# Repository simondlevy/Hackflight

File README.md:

# Intro

Hackflight is a minimalist software toolkit for building multirotor flight
controllers and simulators.  It is geared toward people like me who want to
tinker with flight-control firmware, and use it to teach students about ideas
like
[state estimation](https://simondlevy.github.io/ekf-tutorial)
and
[PID control](https://en.wikipedia.org/wiki/Proportional%E2%80%93integral%E2%80%93derivative_controller).
<b>If you are in the 99% percent of
users who just want to get your vehicle flying without getting into firmware
hacking, I recommend [Betaflight](http://betaflight.com/)</b> (great for
getting started when you're on a budget)
<b>the [Ardupilot](http://copter.ardupilot.org) system</b> (for
sophisticated mission planning with waypoint navigation and the like), or
the <b>[Crazyflie](https://www.bitcraze.io/products/old-products/crazyflie-2-1/)</b>
platform, for a safe, inexpensive introduction to quadcopters as a research
platform.   In addition to big user communities and loads of great features,
these platforms have safety mechanisms that Hackflight lacks, which will help
avoid injury to you and damage to your vehicle.

# Design principles

Hackflight attempts to maintain a simple relationship between
the code and the elements of the flight-control dataflow diagram shown below.
Boxes represent data, ovals represent functions, and feedback arrows
represent the need for functions that have state; for
example, the maintenance of an error integral in a PID controller:

By using header-only C++ classes whenever possible, avoiding C-style macros,
[null pointers](https://www.infoq.com/presentations/Null-References-The-Billion-Dollar-Mistake-Tony-Hoare/),
inheritance, and mutation in favor of
[functional style](https://queue.acm.org/detail.cfm?id=2038036i),
and relying on existing Arduino libraries for sensors and actuators,
Hackflight supports a
[composable](https://www.progress.com/blogs/what-composability-why-should-you-care)
approach to taming the complexity of flight control. The Hackflight [codebase](src/) is
under 3,000 lines of code.

# Hardware

* MCU: [Teensy4.0](https://www.pjrc.com/store/teensy40.html)

* IMU: [BMI088 I^2C breakout board](https://www.tindie.com/products/bobbiebots/bmi088-i2c-breakout)

* Receiver: [OMGS3 ESP32](https://unexpectedmaker.com/shop.html#!/OMGS3/p/687192227)

* Transmitter: Radiomaster T8L modified with [custom circuit board](kicad/tx) using
[TinyS3 ESP32](https://www.adafruit.com/product/5398)

* Telemetry dongle: [TinyPICO ESP32](https://www.adafruit.com/product/5028)

# Simulator

For flight simulation, Hackflight uses [Webots](https://cyberbotics.com/),
a free, open-source robotics simulator. Click [here](webots/apex2) to get started.

# Citing Hackflight

Please cite Hackflight as:

```
@ARTICLE{10.3389/fnbot.2020.00016,
AUTHOR={Levy, Simon D.},   
TITLE={Robustness Through Simplicity: A Minimalist Gateway to Neurorobotic Flight},      
JOURNAL={Frontiers in Neurorobotics},      
VOLUME={14},           
YEAR={2020},      
URL={https://www.frontiersin.org/articles/10.3389/fnbot.2020.00016},       
DOI={10.3389/fnbot.2020.00016},      
ISSN={1662-5218}
}
```

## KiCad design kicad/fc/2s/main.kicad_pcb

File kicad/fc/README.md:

# BOM

* 4-in-1 ESC with motor/power connector and rubber grommets

* Teensy 4.0

* BMI088 breakout

* [Pololu 5V Step-Up/Step-Down Voltage Regulator S7V7F5](https://www.pololu.com/product/2119)

* [1.25mm Pitch JST Molex Picoblade connectors and Pre-Crimped Cables](https://www.amazon.com/dp/B07S18D3RN)

* [LED](https://lighthouseleds.com/1-8mm-2mm-led-red-ultra-bright.html)

* [8-pin 1.25mm Pitch JST Molex Picoblade connector, male pins, right angle](https://www.digikey.com/en/products/detail/molex/0530480810/242870)

* [M2 nylon screws, nuts, and standoffs](https://www.amazon.com/dp/B07D78PFQL)

* Resistors: 100 Ohm, 1000 Ohm, 3300 Ohm

* 1x14 0.1" pitch male header pins

# Build instuctions

Note: I recommend using Scotch tape to mask the pins you're not currently
soldering, and doing a continuity check for bridges/shorts after each step.

Main Board

1. Solder BMI088 breakout to front of board.

2. Solder voltage regulator on back.

3. Solder 1x14 headers on front.

4. Solder the three resistors on back.

5. Solder the LED on front

6. Solder the 4-in-1 ESC cables on the bottom.

7. Build the hover-deck cable using an 8-pin Picoblade connector and pre-crimped cables.

8. Mount the flight controller to the airframe with four M2 screws and nuts, and rubber grommets.

9. After covering the Teensy 4.00 bottom middle with electrical tape to
insulate it from any conact with the components on the flight controller,
solder the Teensy 4.0 onto the header pins on the flight controller. 

Hover Deck: Solder right-angle male PicoBlade connector to board

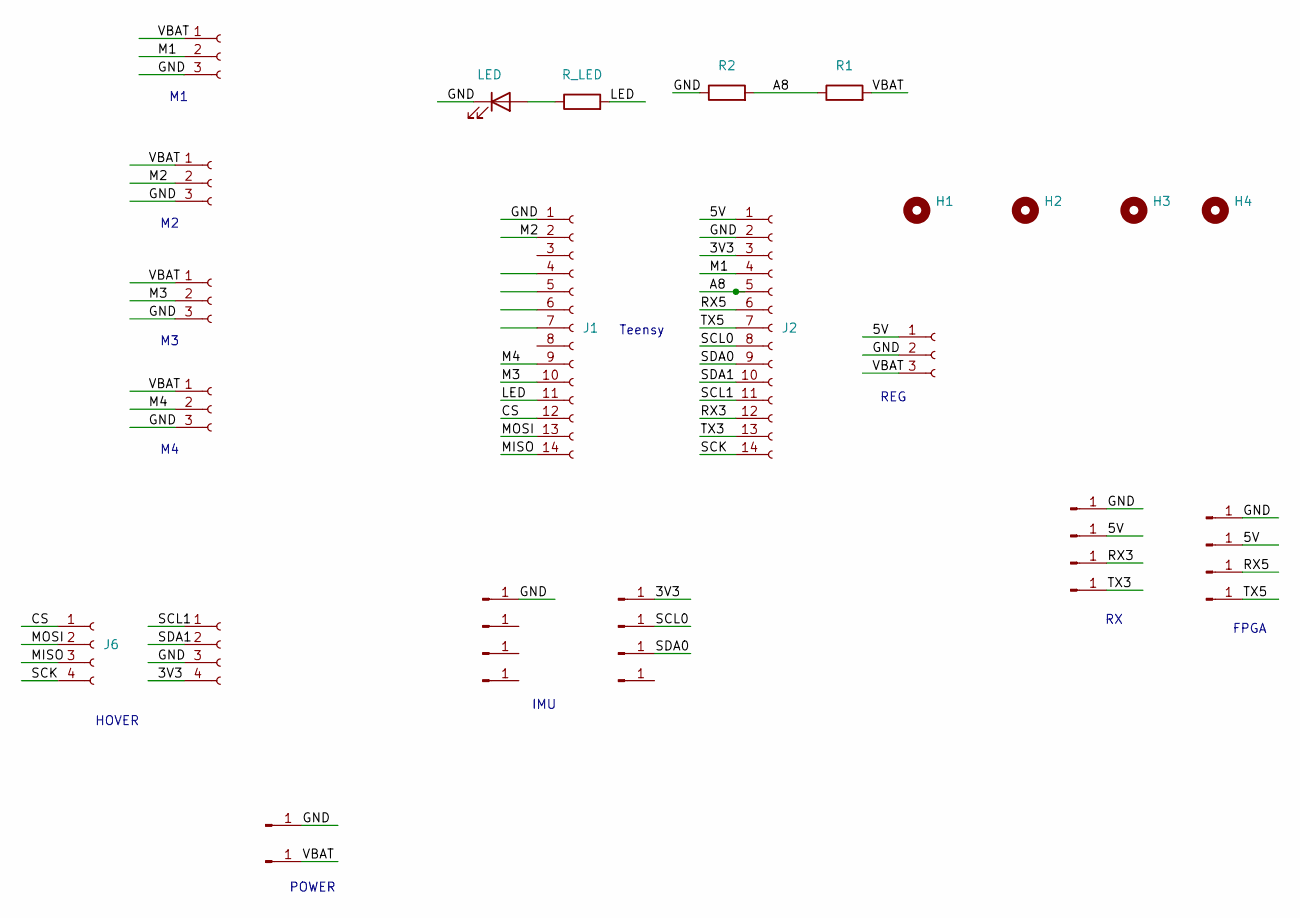
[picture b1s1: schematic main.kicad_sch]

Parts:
D1: LED; LED_D3.0mm_FlatTop
H1, H2, H3, H4: MountingHole; MountingHole_2.5mm
J1: Conn_01x14; PinSocket_1x14_P2.54mm_Vertical
J2: Conn_01x14_Socket; PinSocket_1x14_P2.54mm_Vertical
J3, J5, J7, J8, J9, J10, J11, J12, J13, J14, J17, J18, J19, J20, J21, J22: Conn_01x01_Pin; SolderWirePad_1x01_SMD_1x2mm
J4, J15, J16, J23, J24: Conn_01x03_Socket; PinHeader_1x03_P2.54mm_Vertical
J6, J27: Conn_01x04_Socket; PinHeader_1x04_P2.54mm_Vertical
J25, J26: Conn_01x01_Pin; SolderWirePad_1x01_SMD_2x4mm
R1: R_LED; R_Axial_DIN0204_L3.6mm_D1.6mm_P7.62mm_Horizontal
R2: R1; R_Axial_DIN0204_L3.6mm_D1.6mm_P7.62mm_Horizontal
R3: R2; R_Axial_DIN0204_L3.6mm_D1.6mm_P7.62mm_Horizontal

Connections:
/3V3: J2.3, J10.1 (Pin_1_1), J27.4
/5V: J2.1, J4.1, J14.1 (Pin_1_1), J20.1 (Pin_1_1)
/A8: J2.5, R2.1, R3.2
/CS: J1.12, J6.1
/GND: D1.1 (K), J1.1, J2.2, J3.1 (Pin_1_1), J4.2, J5.1 (Pin_1_1), J15.3, J16.3, J19.1 (Pin_1_1), J23.3, J24.3, J25.1 (Pin_1_1), J27.3, R3.1
/LED: J1.11, R1.2
/M1: J2.4, J15.2
/M2: J1.2, J16.2
/M3: J1.10, J23.2
/M4: J1.9, J24.2
/MISO: J1.14, J6.3
/MOSI: J1.13, J6.2
/RX3: J2.12, J17.1 (Pin_1_1)
/RX5: J2.6, J21.1 (Pin_1_1)
/SCK: J2.14, J6.4
/SCL0: J2.8, J11.1 (Pin_1_1)
/SCL1: J2.11, J27.1
/SDA0: J2.9, J12.1 (Pin_1_1)
/SDA1: J2.10, J27.2
/TX3: J2.13, J18.1 (Pin_1_1)
/TX5: J2.7, J22.1 (Pin_1_1)
/VBAT: J4.3, J15.1, J16.1, J23.1, J24.1, J26.1 (Pin_1_1), R2.2
unnamed: D1.2 (A), R1.1

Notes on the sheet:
FPGA
IMU
REG
Teensy
POWER
HOVER

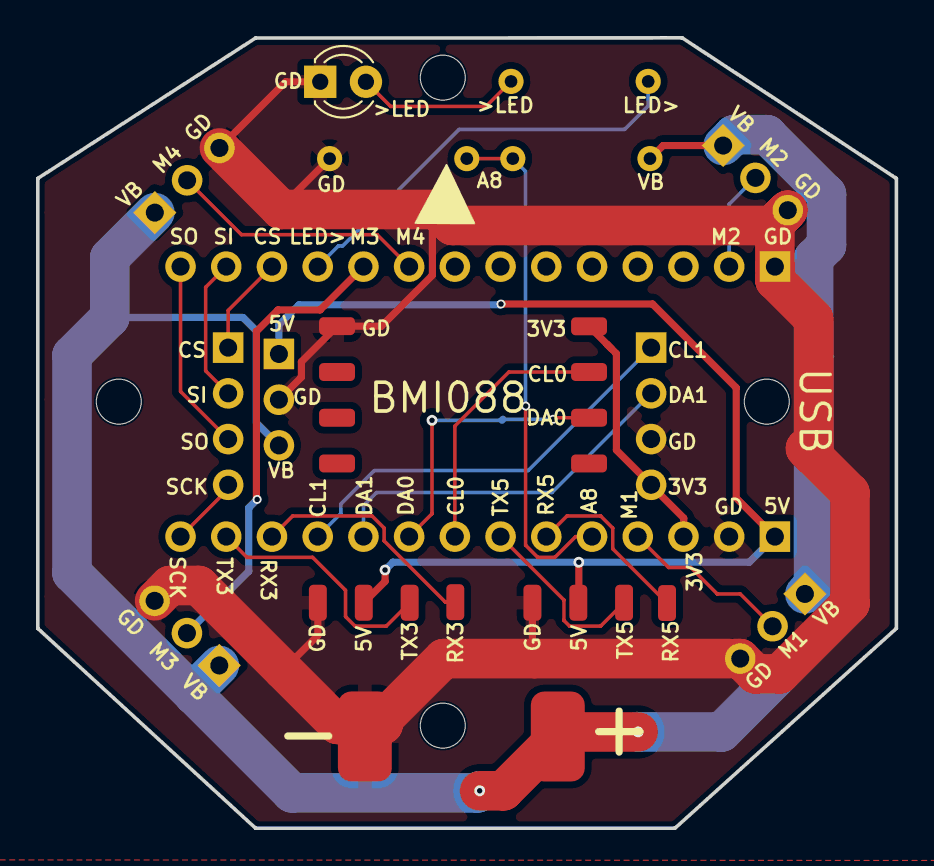
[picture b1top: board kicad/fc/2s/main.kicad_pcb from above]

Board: 2 copper layers, 47.7 x 43.9 mm, 36 parts (0 on the bottom side), 23 nets.

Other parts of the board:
R3#2: R2; R_Axial_DIN0204_L3.6mm_D1.6mm_P7.62mm_Horizontal

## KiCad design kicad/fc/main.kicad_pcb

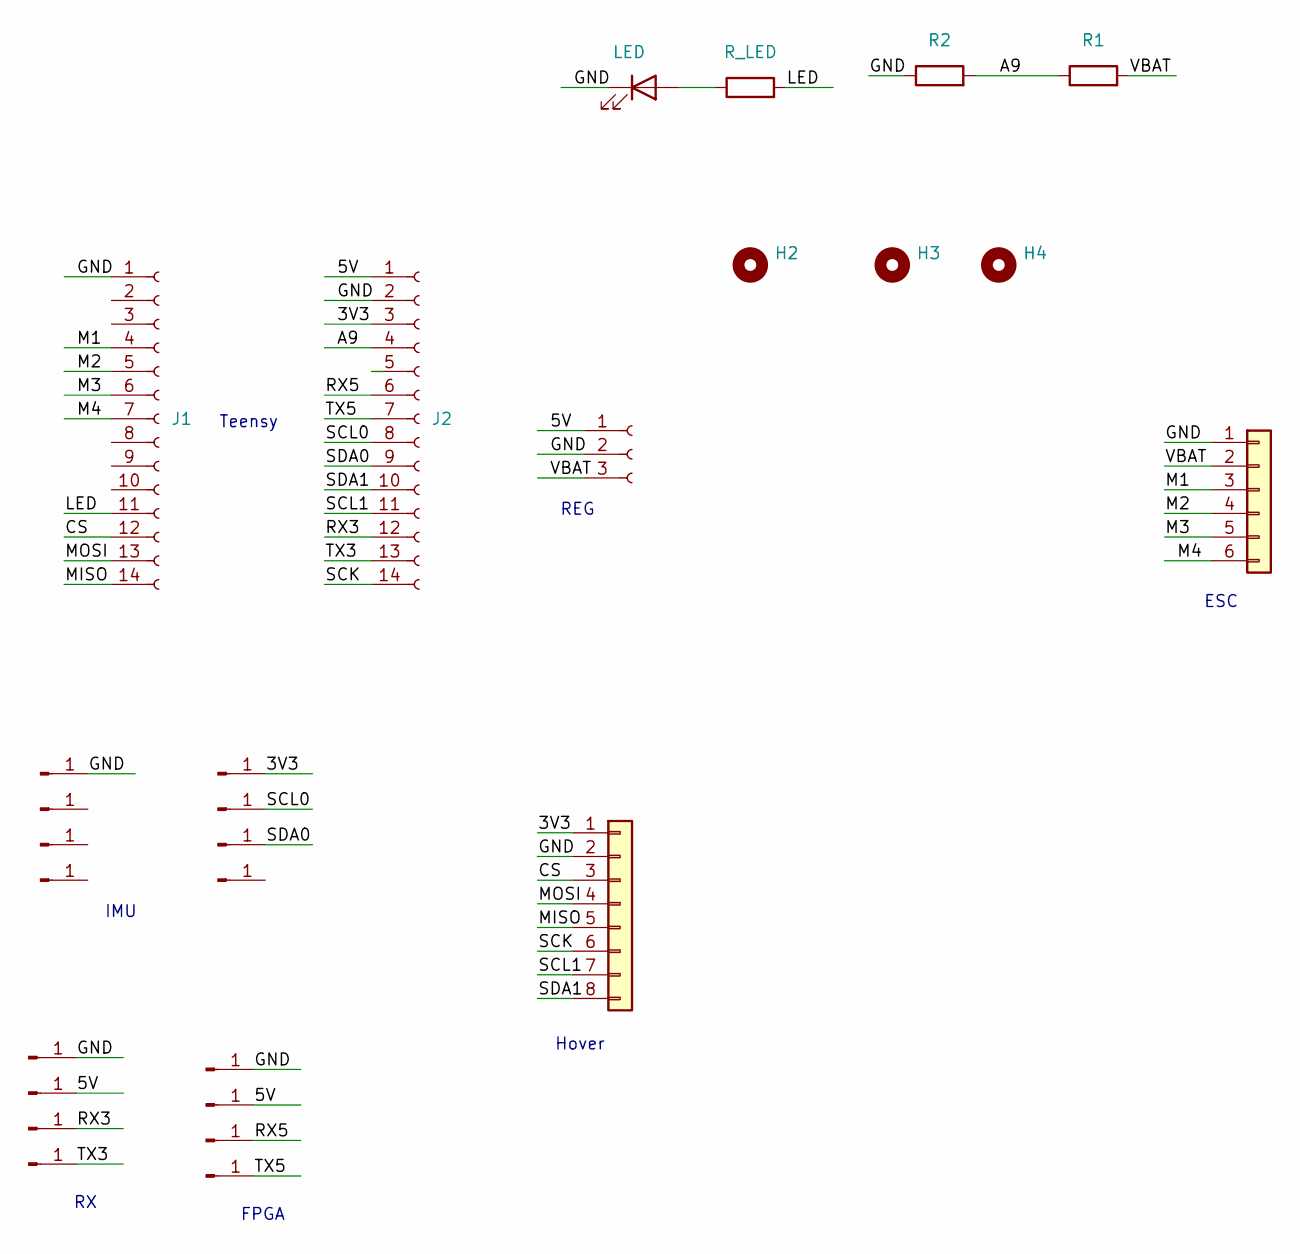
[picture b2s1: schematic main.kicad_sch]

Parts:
D1: LED; LED_D3.0mm_FlatTop
H2, H3, H4: MountingHole; MountingHole_2.5mm
J1: Conn_01x14; PinSocket_1x14_P2.54mm_Vertical
J2: Conn_01x14_Socket; PinSocket_1x14_P2.54mm_Vertical
J3, J5, J7, J8, J9, J10, J11, J12, J13, J14, J17, J18, J19, J20, J21, J22: Conn_01x01_Pin; SolderWirePad_1x01_SMD_1x2mm
J4: Conn_01x03_Socket; PinHeader_1x03_P2.54mm_Vertical
J6: Conn_01x08; PinSocket_1x08_P2.00mm_Vertical
J23: Conn_01x06; PinSocket_1x06_P2.00mm_Vertical
R1: R_LED; R_Axial_DIN0204_L3.6mm_D1.6mm_P7.62mm_Horizontal
R2: R1; R_Axial_DIN0204_L3.6mm_D1.6mm_P7.62mm_Horizontal
R3: R2; R_Axial_DIN0204_L3.6mm_D1.6mm_P7.62mm_Horizontal

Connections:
/3V3: J2.3, J6.1, J10.1 (Pin_1_1)
/5V: J2.1, J4.1, J14.1 (Pin_1_1), J20.1 (Pin_1_1)
/A9: J2.4, R2.1, R3.2
/CS: J1.12, J6.3
/GND: D1.1 (K), J1.1, J2.2, J3.1 (Pin_1_1), J4.2, J5.1 (Pin_1_1), J6.2, J19.1 (Pin_1_1), J23.1, R3.1
/LED: J1.11, R1.2
/M1: J1.4, J23.3
/M2: J1.5, J23.4
/M3: J1.6, J23.5
/M4: J1.7, J23.6
/MISO: J1.14, J6.5
/MOSI: J1.13, J6.4
/RX3: J2.12, J17.1 (Pin_1_1)
/RX5: J2.6, J21.1 (Pin_1_1)
/SCK: J2.14, J6.6
/SCL0: J2.8, J11.1 (Pin_1_1)
/SCL1: J2.11, J6.7
/SDA0: J2.9, J12.1 (Pin_1_1)
/SDA1: J2.10, J6.8
/TX3: J2.13, J18.1 (Pin_1_1)
/TX5: J2.7, J22.1 (Pin_1_1)
/VBAT: J4.3, J23.2, R2.2
unnamed: D1.2 (A), R1.1

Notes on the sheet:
IMU
REG
Hover
Teensy
ESC
FPGA

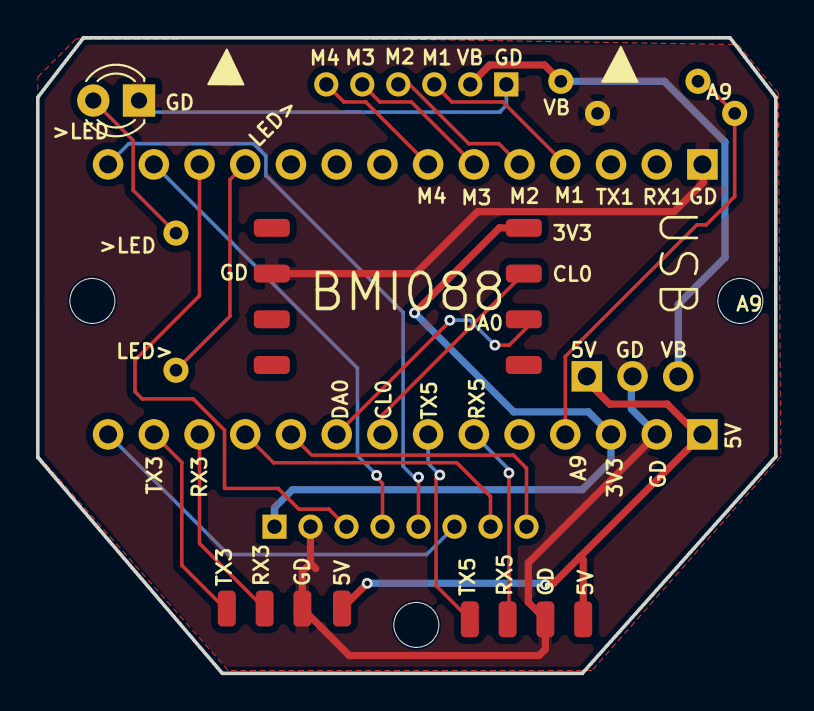
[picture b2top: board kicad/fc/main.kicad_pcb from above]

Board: 2 copper layers, 41.0 x 35.3 mm, 28 parts (0 on the bottom side), 23 nets.

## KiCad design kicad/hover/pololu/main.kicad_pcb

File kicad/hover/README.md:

# BOM

Note: I recommend using Scotch tape to mask the pins you're not currently
soldering.

* [VL53L1 proximity sensor](https://www.tindie.com/products/onehorse/vl53l1-long-range-proximity-sensor/)

* [PMW3901 optical-flow sensor](https://www.tindie.com/products/onehorse/pmw3901-optical-flow-sensor/)

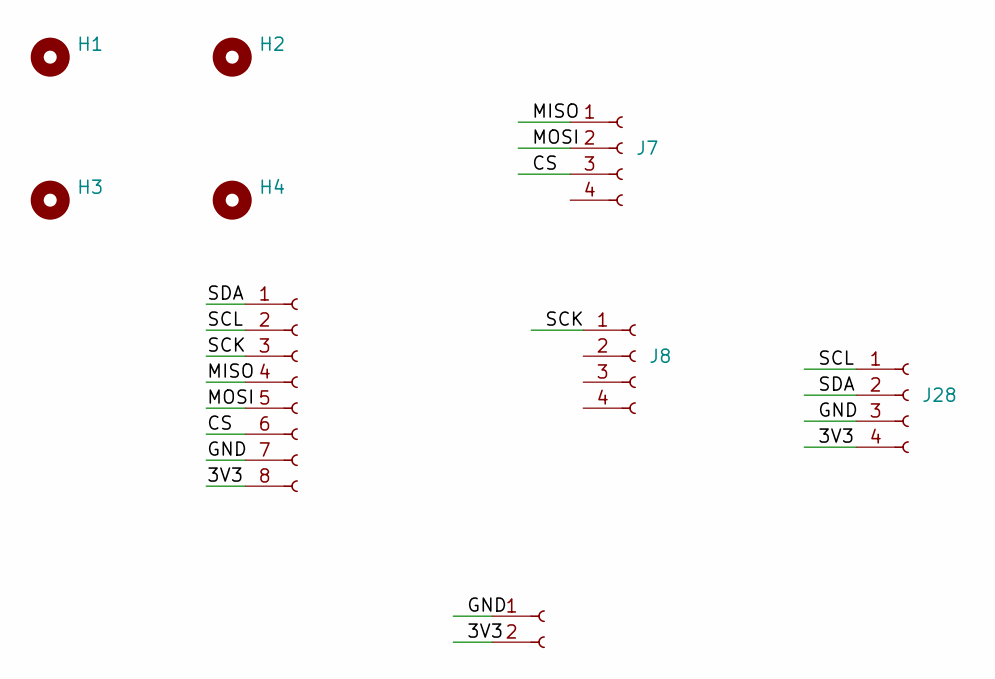
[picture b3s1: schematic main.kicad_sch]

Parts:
H1, H2, H3, H4: MountingHole; MountingHole_2.5mm
J1: Conn_01x02_Socket; PinHeader_1x02_P2.54mm_Vertical
J4: Conn_01x08_Socket; PinHeader_1x08_P1.27mm_Vertical
J7, J8, J28: Conn_01x04_Socket; PinHeader_1x04_P2.54mm_Vertical

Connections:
/3V3: J1.2, J4.8, J28.4
/CS: J4.6, J7.3
/GND: J1.1, J4.7, J28.3
/MISO: J4.4, J7.1
/MOSI: J4.5, J7.2
/SCK: J4.3, J8.1 (Pin_1_1)
/SCL: J4.2, J28.1
/SDA: J4.1, J28.2

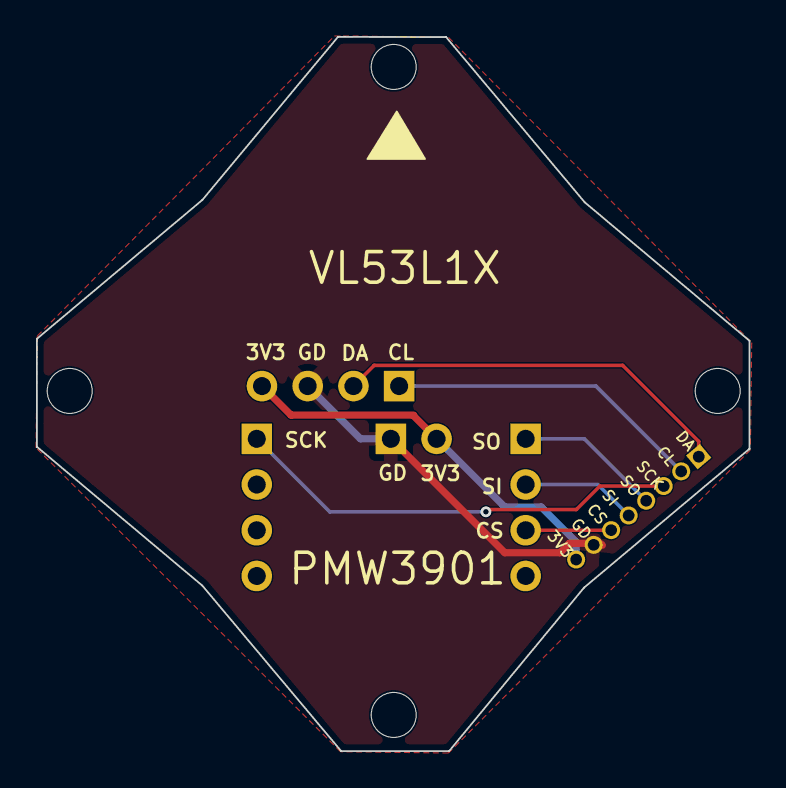
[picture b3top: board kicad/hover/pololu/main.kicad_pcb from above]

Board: 2 copper layers, 39.6 x 39.7 mm, 9 parts (0 on the bottom side), 8 nets.

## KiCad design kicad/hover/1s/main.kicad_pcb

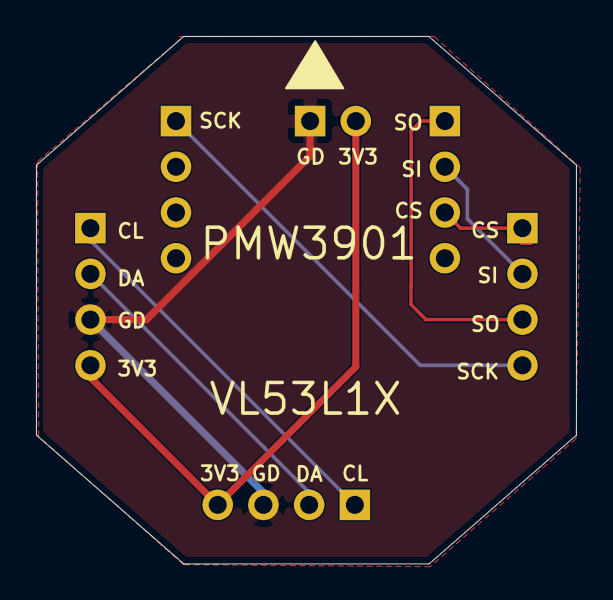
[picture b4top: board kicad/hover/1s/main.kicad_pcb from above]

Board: 2 copper layers, 30.0 x 29.3 mm, 6 parts (0 on the bottom side), 8 nets.

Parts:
J1: Conn_01x02_Socket; PinHeader_1x02_P2.54mm_Vertical
J6, J7, J8, J27, J28: Conn_01x04_Socket; PinHeader_1x04_P2.54mm_Vertical

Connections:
/3V3: J1.2, J27.4, J28.4
/CS: J6.1, J7.3
/GND: J1.1, J27.3, J28.3
/MISO: J6.3, J7.1
/MOSI: J6.2, J7.2
/SCK: J6.4, J8.1 (Pin_1_1)
/SCL: J27.1, J28.1
/SDA: J27.2, J28.2

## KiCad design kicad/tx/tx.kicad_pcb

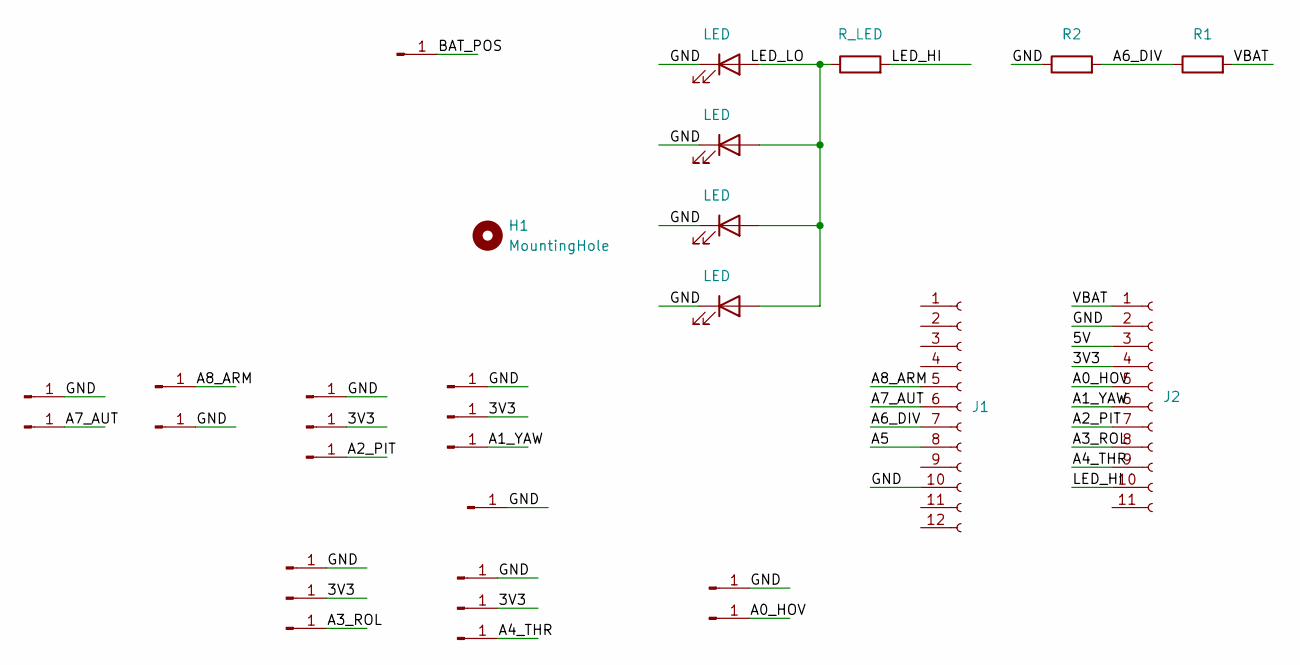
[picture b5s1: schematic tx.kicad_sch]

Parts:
D1, D2, D3, D4: LED; LED_D3.0mm_FlatTop
H1: MountingHole; MountingHole_4mm
J1: Conn_01x12_Socket; PinHeader_1x10_P2.54mm_Vertical
J2: Conn_01x11_Socket; PinHeader_1x11_P2.54mm_Vertical
J5, J6, J7, J8, J9, J10, J11, J12, J13, J14, J15, J16, J17, J18, J19, J20: Conn_01x01_Pin; SolderWirePad_1x01_SMD_2x4mm
J24, J25, J26, J27: Conn_01x01_Pin; PinSocket_1x01_P2.54mm_Vertical
R1: R_LED; R_Axial_DIN0204_L3.6mm_D1.6mm_P7.62mm_Horizontal
R2: R1; R_Axial_DIN0204_L3.6mm_D1.6mm_P7.62mm_Horizontal
R3: R2; R_Axial_DIN0204_L3.6mm_D1.6mm_P7.62mm_Horizontal

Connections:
/3V3: J2.4, J9.1 (Pin_1_1), J10.1 (Pin_1_1), J11.1 (Pin_1_1), J12.1 (Pin_1_1)
/5V: J2.3
/A0_HOV: J2.5, J27.1 (Pin_1_1)
/A1_YAW: J2.6, J16.1 (Pin_1_1)
/A2_PIT: J2.7, J15.1 (Pin_1_1)
/A3_ROL: J2.8, J14.1 (Pin_1_1)
/A4_THR: J2.9, J13.1 (Pin_1_1)
/A5: J1.8
/A6_DIV: J1.7, R2.1, R3.2
/A7_AUT: J1.6, J25.1 (Pin_1_1)
/A8_ARM: J1.5, J18.1 (Pin_1_1)
/BAT_POS: J19.1 (Pin_1_1)
/GND: D1.1 (K), D2.1 (K), D3.1 (K), D4.1 (K), J1.10, J2.2, J5.1 (Pin_1_1), J6.1 (Pin_1_1), J7.1 (Pin_1_1), J8.1 (Pin_1_1), J17.1 (Pin_1_1), J20.1 (Pin_1_1), J24.1 (Pin_1_1), J26.1 (Pin_1_1), R3.1
/LED_HI: J2.10, R1.2
/VBAT: J2.1, R2.2; also elsewhere on the board
unnamed: D1.2 (A), D2.2 (A), D3.2 (A), D4.2 (A), R1.1

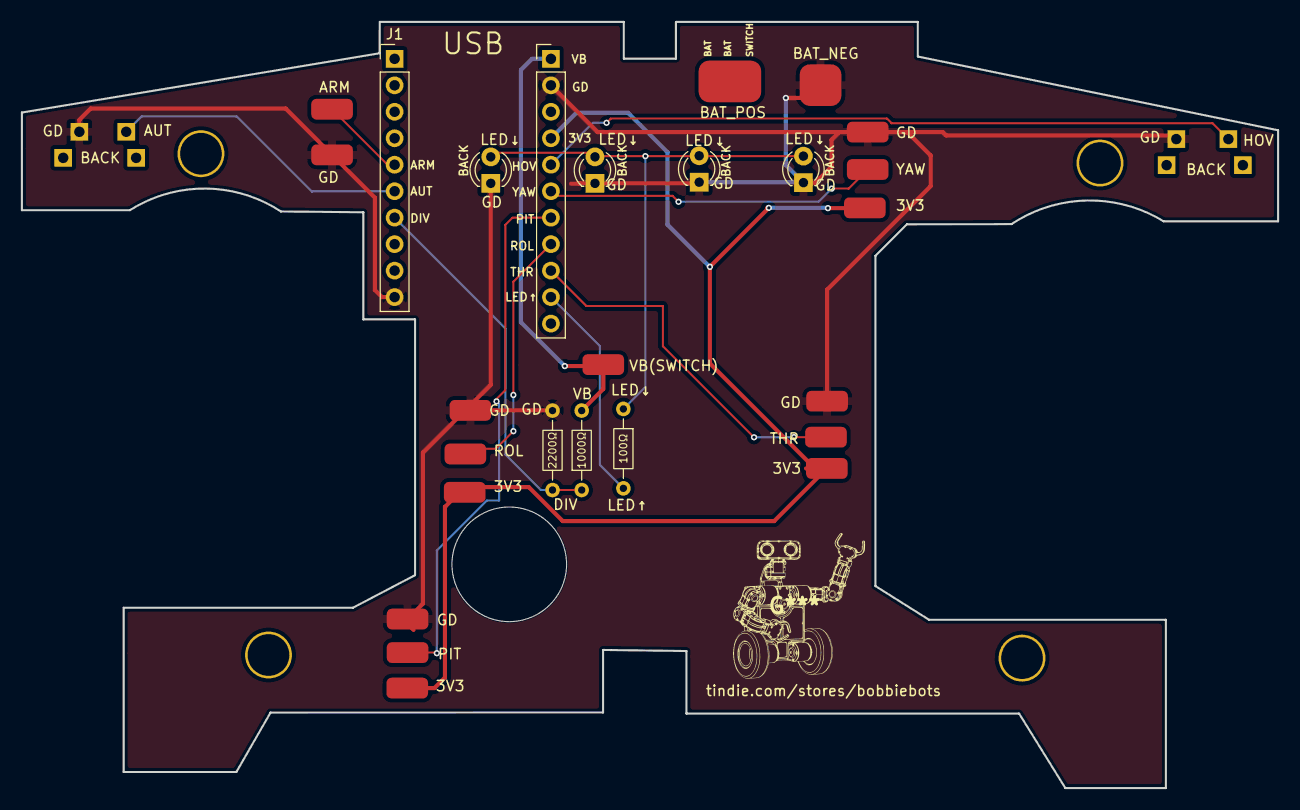
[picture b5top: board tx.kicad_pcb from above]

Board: 2 copper layers, 120.5 x 73.5 mm, 36 parts (0 on the bottom side), 13 nets.

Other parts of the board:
H1#2: MountingHole; MountingHole_4mm
J21: Conn_01x01_Pin; SolderWirePad_1x01_SMD_2x4mm
J28, J29, J30, J31: Conn_01x01_Pin; PinSocket_1x01_P2.54mm_Vertical

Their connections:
/VBAT: J21.1 (Pin_1_1); also elsewhere on the board

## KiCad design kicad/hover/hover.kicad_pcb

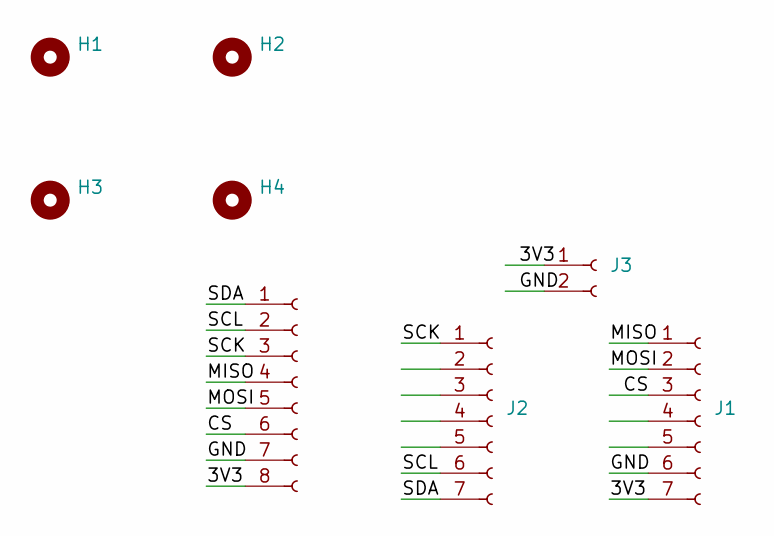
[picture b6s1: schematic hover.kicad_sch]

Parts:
H1, H2, H3, H4: MountingHole; MountingHole_2.5mm
J1, J2: Conn_01x07_Socket; PinSocket_1x07_P2.54mm_Vertical
J3: Conn_01x02_Socket; PinSocket_1x02_P2.54mm_Vertical
J4: Conn_01x08_Socket; Molex_PicoBlade_53048-0810_1x08_P1.25mm_Horizontal

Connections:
/3V3: J1.7, J3.1, J4.8
/CS: J1.3, J4.6
/GND: J1.6, J3.2, J4.7
/MISO: J1.1, J4.4
/MOSI: J1.2, J4.5
/SCK: J2.1, J4.3
/SCL: J2.6, J4.2
/SDA: J2.7, J4.1

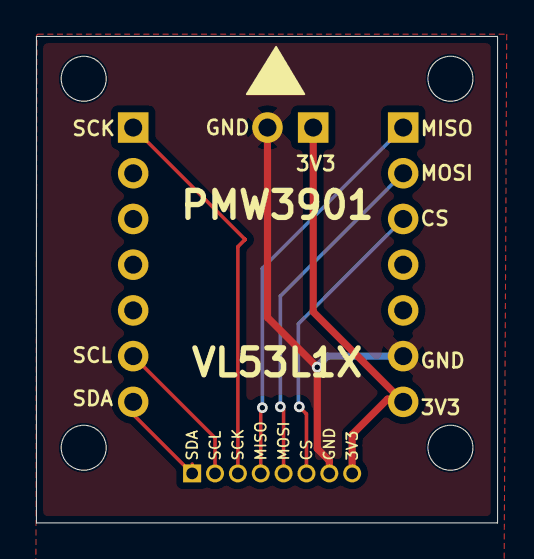
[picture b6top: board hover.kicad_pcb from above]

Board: 2 copper layers, 25.6 x 27.0 mm, 8 parts (0 on the bottom side), 8 nets.
